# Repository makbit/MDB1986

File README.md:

## MDB1986 - Milandr Development Board for [K1986BE1QI MCU (package LQFP-144)](https://ic.milandr.ru/products/mikrokontrollery_i_protsessory/32_razryadnye_mikrokontrollery/1986vekh_avia/k1986ve1t/).
> This is an open source hardware project for tutorial purposes.

The PCB was designed in the Eagle CAD 9.0.

The [`Blink103`](Blink103) folder contains firmware for on-board debugger MCU (STM32F103). It can be used to test debugger curcuit and target MCU with JTAG IDCODE instruction. Project files were created with the [Keil uVision MDK](https://www.keil.com/demo/eval/arm.htm). The board schematics can be found in [`MDB1986-Schema.png`](MDB1986-Schema.png) file.

### MDB198 Development Board :cool:

## TODO :pen:
- [x] Solder the board :+1:
- [x] Download debugger firmware
- [x] Install [MDR Library Pack](https://ic.milandr.ru/soft/)
- [ ] Build and run Demo test
- [ ] Publish articles!

[GitHub readme tips&tricks](https://help.github.com/articles/basic-writing-and-formatting-syntax/)

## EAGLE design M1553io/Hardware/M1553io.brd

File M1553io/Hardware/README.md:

# M1553io - MIL_STD_1553 input/output shield for MDB1986 Development Board.

This is a simple adapter for connecting the MDB1986 board to the MIL_STD_1553 bus.
It is based on the 5559UH13YA transciever chip by NPO "Physica". This component and transformer can be found in the 5559.lbr file.

##### The adapter board:

##### The adapter schematics:

### TODO :pen:
- [ ] Use small package for 74xxx ICC as a level-shifter;
- [ ] P_EN pin should be pulled-down (or up);
- [ ] Check the length of the transformer pins;
- [ ] Add check-points (pin) for Logic-Analyzer;
- [ ] Place all components on the new Development Board;

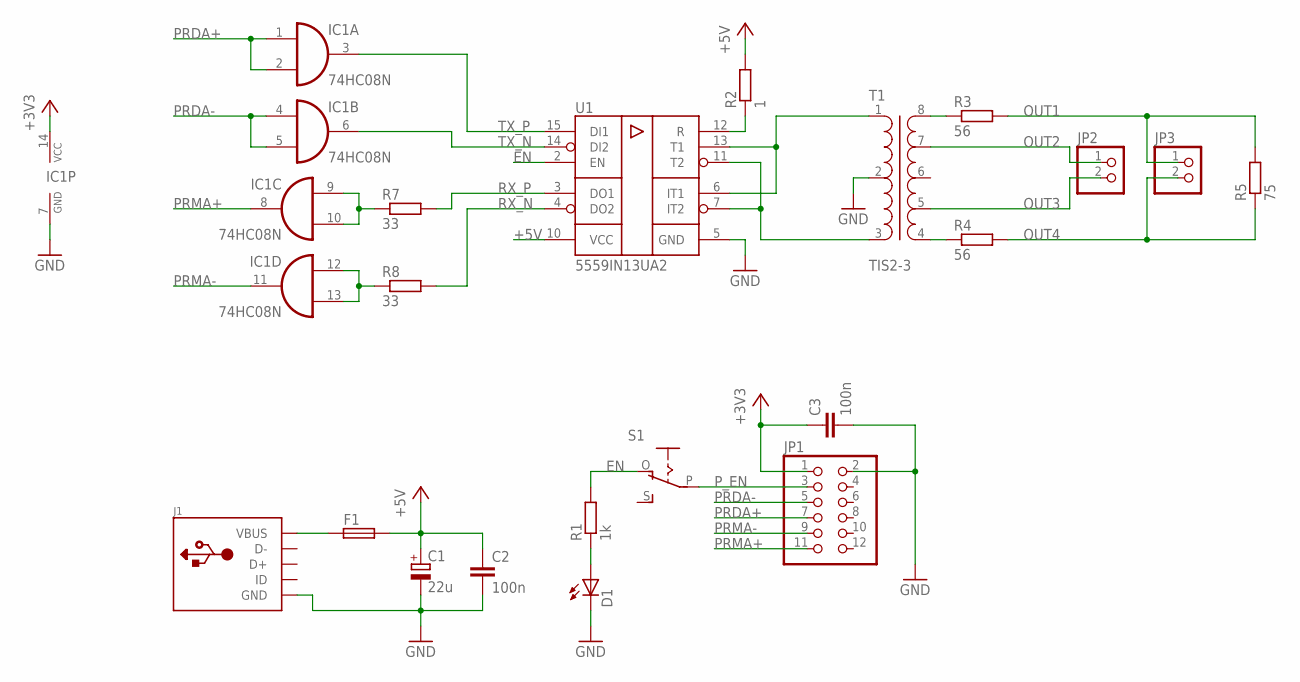
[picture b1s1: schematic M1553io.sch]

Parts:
C1: 22u; RCL-1206F-POL
C2, C3: 100n; RCL-1206F
D1: LED1206; LED-1206F
F1: FUSE-NSMF; RCL-1206F
IC1: 74HC08N; DIL14
J1: USB-MINI; USB-MINIB
JP1: PINHD-2X6; 2X06
JP2, JP3: PINHD-1X2; 1X02
R1: 1k; RCL-0805F
R2: 1; RCL-0805F
R3, R4: 56; RCL-0805F
R5: 75; RCL-0805F
R7, R8: 33; RCL-0805F
S1: EG1218S; EG1218
T1: TIS2-3
U1: 5559IN13UA2; 5119.16-A

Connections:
+3V3: C3.1, IC1.14 (VCC), JP1.1
+5V: C1.+, C2.1, F1.2, R2.2, U1.10 (VCC)
EN: R1.2, S1.O, U1.2 (EN)
GND: C1.-, C2.2, C3.2, D1.C, IC1.7 (GND), J1.GND, JP1.2, T1.2, U1.5 (GND)
unnamed: R3.1, T1.8
unnamed: R4.1, T1.4
unnamed: R2.1, U1.12 (R)
unnamed: F1.1, J1.VBUS
unnamed: D1.A, R1.1
unnamed: IC1.9 (I0), IC1.10 (I1), R7.1
unnamed: IC1.12 (I0), IC1.13 (I1), R8.1
OUT1: JP3.1, R3.2, R5.2
OUT2: JP2.1, T1.7
OUT3: JP2.2, T1.5
OUT4: JP3.2, R4.2, R5.1
PRDA+: IC1.1 (I0), IC1.2 (I1), JP1.7
PRDA-: IC1.4 (I0), IC1.5 (I1), JP1.5
PRMA+: IC1.8 (O), JP1.11
PRMA-: IC1.11 (O), JP1.9
P_EN: JP1.3, S1.P
RX_N: R8.2, U1.4 (DO2)
RX_P: R7.2, U1.3 (DO1)
T1: T1.1, U1.6 (IT1), U1.13 (T1)
T2: T1.3, U1.7 (IT2), U1.11 (T2)
TX_N: IC1.6 (O), U1.14 (DI2)
TX_P: IC1.3 (O), U1.15 (DI1)

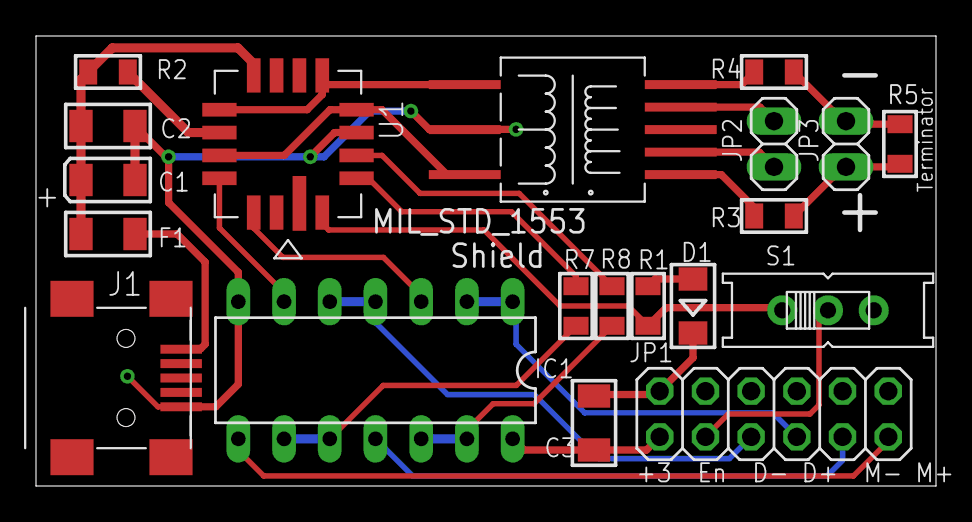
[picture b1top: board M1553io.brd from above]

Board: 2 copper layers, 50.0 x 25.0 mm, 20 parts (0 on the bottom side), 26 nets.

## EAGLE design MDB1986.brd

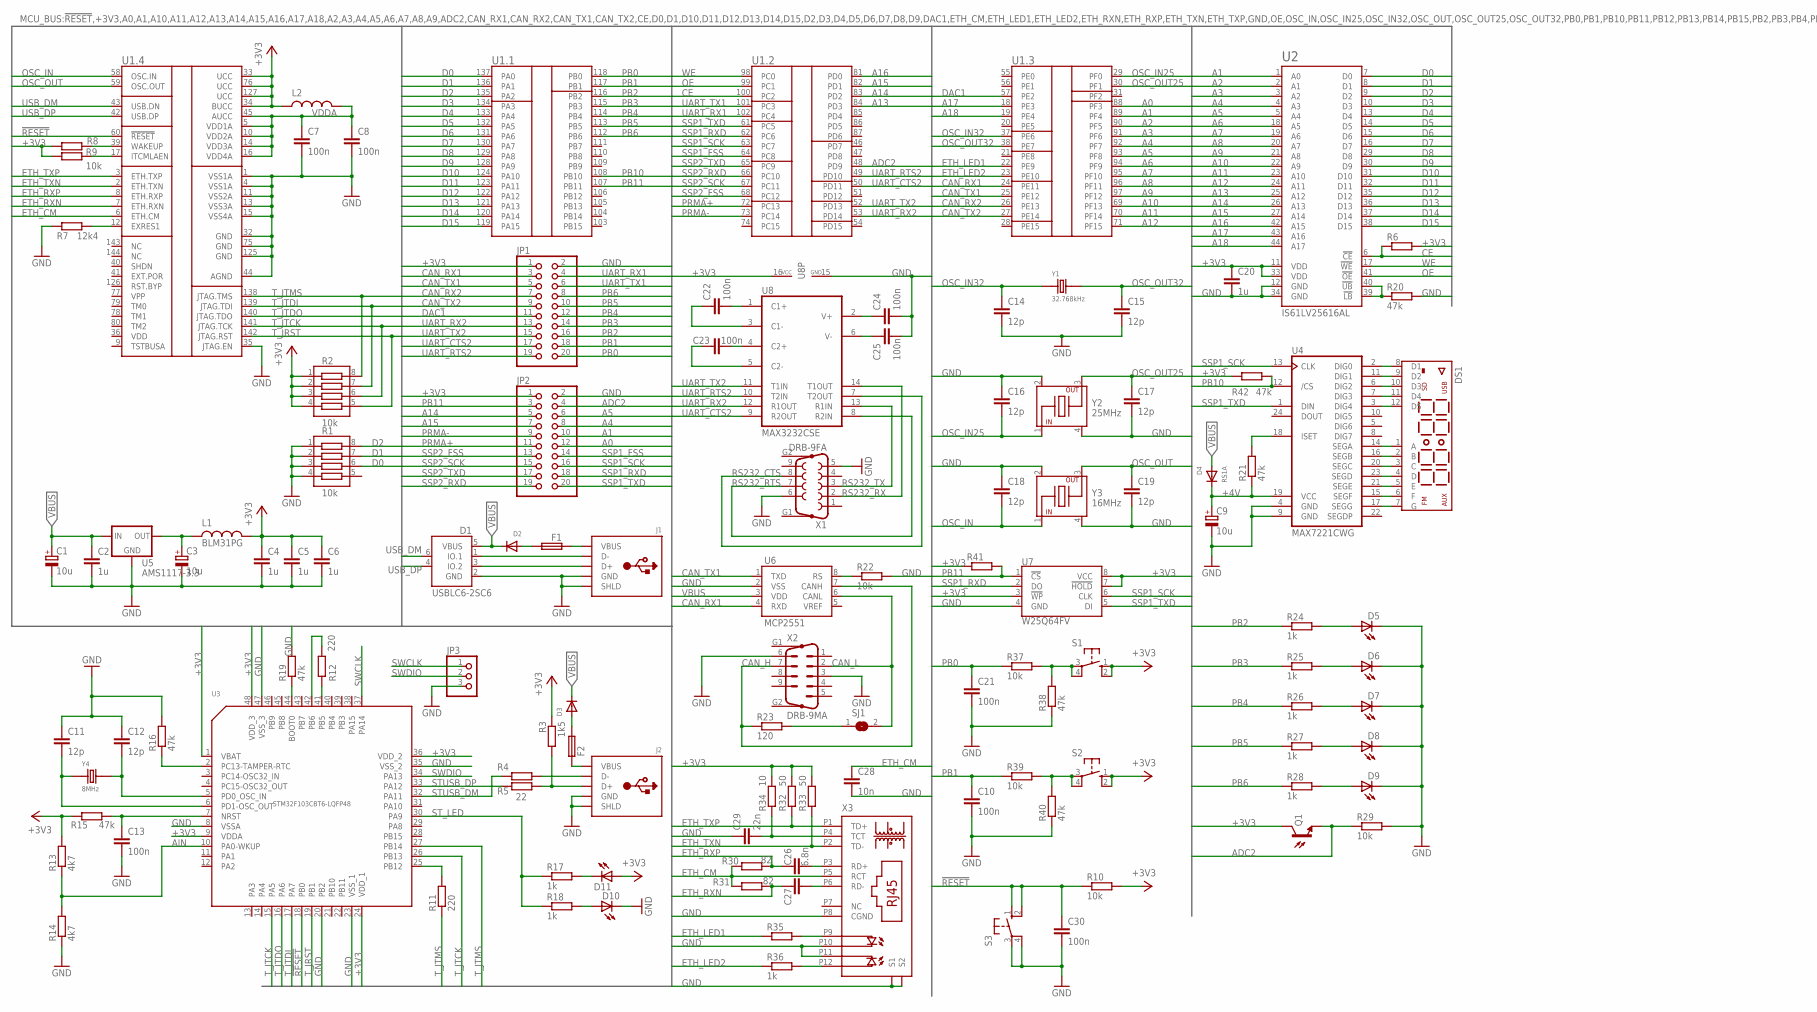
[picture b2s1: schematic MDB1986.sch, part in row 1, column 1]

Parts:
C1, C3, C9: 10u; RCL-1206F-POL
C2, C4, C5, C6, C20: 1u; RCL-0805F
C7, C8, C10, C13, C21, C22, C23, C24, C25, C30: 100n; RCL-0805F
C11, C12, C14, C15, C16, C17, C18, C19: 12p; RCL-0805F
C26: 6.8n; RCL-0805F
C27: C-EU0805; RCL-0805F
C28: 10n; RCL-0805F
C29: 22n; RCL-0805F
D1: USBLC6-2SC6; SOT-23-6L
D2, D3: DIODEDO-214(SMB); DO-214AA(SMB)
D4: RS1A; DO-214AC(SMA)
D5, D6, D7, D8, D9, D10, D11: LED1206; LED-1206F
DS1: LED-7SEG-12PIN-CC; LED-7SEG-12P2.54
F1, F2: FUSE-NSMF; RCL-1206F
J1, J2: USB-TYPE-B; USB-TYPE-B-4P
JP1, JP2: PINHD-2X10; 2X10
JP3: PINHD-1X3; 1X03
L1: BLM31PG; RCL-1206F
L2: L-EU1206; RCL-1206F
Q1: PHOTOTRANSISTORPT17-21C-L41-TR8; PT17-21C-L41-TR8
R1, R2: 10k; RA-1206-X4
R3: 1k5; RCL-0805F
R4, R6, R8, R35, R41: R-EU0805; RCL-0805F
R5: 22; RCL-0805F
R7: 12k4; RCL-0805F
R9, R10, R22, R29, R37, R39: 10k; RCL-0805F
R11, R12: 220; RCL-0805F
R13, R14: 4k7; RCL-0805F
R15, R16, R19, R20, R21, R38, R40, R42: 47k; RCL-0805F
R17, R18, R24, R25, R26, R27, R28, R36: 1k; RCL-0805F
R23: 120; RCL-0805F
R30, R31: 82; RCL-0805F
R32, R33: 50; RCL-0805F
R34: 10; RCL-0805F
S1, S2, S3: SWITCH-10-XX; BUTTON-B3F-10XX
SJ1: SJ
U1: MCU-K1986BE1QI; LQFP144-0.5-20X20M
U2: IS61LV25616AL; TSOP2-44-400BF
U3: STM32F103CBT6-LQFP48; LQFP48-0.5-7X7MM
U4: MAX7221CWG; SO24W
U5: AMS1117-3.3; SOT223
U6: MCP2551; SO08
U7: W25Q64FV; SOIC-8
U8: MAX3232CSE; SO16
X1: DRB-9FA; F09HP
X2: DRB-9MA; M09HP
X3: HR911105A; RJ45
Y1: 32.768kHz; XTAL-FC-135
Y2: 25MHz; XTAL-FA-238
Y3: 16MHz; XTAL-FA-238
Y4: 8MHz; XTAL-NX3225

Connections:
!RESET: C30.1, R10.1, S3.1 (S), S3.2 (S1), U1.60 (!RESET), U3.18 (PB0)
+3V3: C4.1, C5.1, C6.1, C20.1, D11.A, JP1.1, JP2.1, L1.2, L2.1, Q1.C, R2.1 (P.1), R2.2 (P.2), R2.3 (P.3), R2.4 (P.4), R3.1, R6.2, R8.1, R9.1, R10.2, R13.2, R15.1, R32.2, R33.2, R34.2, R41.1, R42.1, S1.1 (S), S1.2 (S1), S2.1 (S), S2.2 (S1), U1.33 (UCC), U1.34 (BUCC), U1.76 (UCC), U1.127 (UCC), U2.11 (VDD), U2.33 (VDD), U3.1 (VBAT), U3.9 (VDDA), U3.24 (VDD_1), U3.36 (VDD_2), U3.48 (VDD_3), U7.3 (!WP), U7.7 (!HOLD), U7.8 (VCC), U8.16 (VCC)
+4V: C9.+, D4.C, R21.1, U4.19 (VCC)
A0: JP2.12, U1.88 (PF3)
A1: JP2.10, U1.89 (PF4), U2.1 (A0)
A2: U1.90 (PF5), U2.2 (A1)
A3: U1.91 (PF6), U2.3 (A2)
A4: JP2.8, U1.92 (PF7), U2.4 (A3)
A5: JP2.6, U1.93 (PF8), U2.5 (A4)
A6: U1.94 (PF9), U2.18 (A5)
A7: U1.95 (PF10), U2.19 (A6)
A8: U1.96 (PF11), U2.20 (A7)
A9: U1.97 (PF12), U2.21 (A8)
A10: U1.69 (PF13), U2.22 (A9)
A11: U1.70 (PF14), U2.23 (A10)
A12: U1.71 (PF15), U2.24 (A11)
A13: U1.84 (PD3), U2.25 (A12)
A14: JP2.5, U1.83 (PD2), U2.26 (A13)
A15: JP2.7, U1.82 (PD1), U2.27 (A14)
A16: U1.81 (PD0), U2.42 (A15)
A17: U1.18 (PE3), U2.43 (A16)
A18: U1.19 (PE4), U2.44 (A17)
ADC2: JP2.4, Q1.E, R29.1, U1.48 (PD9)
AIN: R13.1, R14.2, U3.10 (PA0-WKUP)
BOOT0: R19.1, U3.44 (BOOT0)
CAN_H: R23.1, U6.7 (CANH), X2.7
CAN_L: SJ1.2, U6.6 (CANL), X2.2
CAN_RX1: JP1.3, U1.24 (PE11), U6.4 (RXD)
CAN_RX2: JP1.7, U1.26 (PE13)
CAN_TX1: JP1.5, U1.25 (PE12), U6.1 (TXD)
CAN_TX2: JP1.9, U1.27 (PE14)
CE: R6.1, U1.100 (PC2), U2.6 (!CE)
D0: R1.6 (P.6), U1.137 (PA0), U2.7 (D0)
D1: R1.7 (P.7), U1.136 (PA1), U2.8 (D1)
D2: R1.8 (P.8), U1.135 (PA2), U2.9 (D2)
D3: U1.134 (PA3), U2.10 (D3)
D4: U1.133 (PA4), U2.13 (D4)
D5: U1.132 (PA5), U2.14 (D5)
D6: U1.131 (PA6), U2.15 (D6)
D7: U1.130 (PA7), U2.16 (D7)
D8: U1.129 (PA8), U2.29 (D8)
D9: U1.128 (PA9), U2.30 (D9)
D10: U1.124 (PA10), U2.31 (D10)
D11: U1.123 (PA11), U2.32 (D11)
D12: U1.122 (PA12), U2.35 (D12)
D13: U1.121 (PA13), U2.36 (D13)
D14: U1.120 (PA14), U2.37 (D14)
D15: U1.119 (PA15), U2.38 (D15)
DAC1: JP1.11, U1.57 (PE2)
ETH_CM: C28.1, R30.1, R31.1, U1.6 (ETH.CM), X3.P5 (RCT)
ETH_LED1: R35.1, U1.22 (PE9)
ETH_LED2: R36.1, U1.23 (PE10)
ETH_RXN: C27.1, R31.2, U1.7 (ETH.RXN)
ETH_RXP: C26.1, R30.2, U1.8 (ETH.RXP)
ETH_TXN: R33.1, U1.2 (ETH.TXN), X3.P2 (TD-)
ETH_TXP: R32.1, U1.3 (ETH.TXP), X3.P1 (TD+)
GND: C1.-, C2.2, C3.-, C4.2, C5.2, C6.2, C7.2, C8.2, C9.-, C10.2, C11.1, C12.1, C13.2, C14.2, C15.2, C16.1, C17.2, C18.1, C19.2, C20.2, C21.2, C24.2, C25.2, C28.2, C29.1, C30.2, D1.2 (GND), D5.C, D6.C, D7.C, D8.C, D9.C, D10.C, J1.4_GND (GND), J1.M1 (SHLD), J1.M2 (SHLD), J2.4_GND (GND), J2.M1 (SHLD), J2.M2 (SHLD), JP1.2, JP2.2, JP3.3, R1.1 (P.1), R1.2 (P.2), R1.3 (P.3), R1.4 (P.4), R7.1, R14.1, R16.2, R19.2, R20.2, R22.2, R29.2, R38.1, R40.1, S3.3, S3.4 (P1), U1.1 (VSS1A), U1.4 (VSS1A), U1.11 (VSS2A), U1.13 (VSS3A), U1.15 (VSS4A), U1.32 (GND), U1.35 (JTAG.EN), U1.44 (AGND), U1.75 (GND), U1.125 (GND), U2.12 (GND), U2.34 (GND), U3.8 (VSSA), U3.20 (PB2), U3.23 (VSS_1), U3.35 (VSS_2), U3.47 (VSS_3), U4.4 (GND), U4.9 (GND), U5.1 (GND), U6.2 (VSS), U7.4 (GND), U8.15 (GND), X1.5, X1.6, X2.3, X2.6, X3.P8 (CGND), X3.P10 (GLED-), X3.P11 (YLED-), X3.SHIELD1 (S1), X3.SHIELD2 (S2), Y2.2, Y2.4, Y3.2, Y3.4
unnamed: DS1.8 (D1), U4.2 (DIG0)
unnamed: DS1.9 (D2), U4.11 (DIG1)
unnamed: DS1.10 (D3), U4.6 (DIG2)
unnamed: DS1.11 (D4), U4.7 (DIG3)
unnamed: DS1.12 (D5), U4.3 (DIG4)
unnamed: DS1.1 (A), U4.14 (SEGA)
unnamed: DS1.2 (B), U4.16 (SEGB)
unnamed: DS1.3 (C), U4.20 (SEGC)
unnamed: DS1.4 (D), U4.23 (SEGD)
unnamed: DS1.5 (E), U4.21 (SEGE)
unnamed: DS1.6 (F), U4.15 (SEGF)
unnamed: DS1.7 (G), U4.17 (SEGG)
unnamed: F1.1, J1.1_VBUS (VBUS)
unnamed: D2.A, F1.2
unnamed: C12.2, U3.5 (PD0_OSC_IN), Y4.2
unnamed: C11.2, U3.6 (PD1-OSC_OUT), Y4.1
unnamed: R21.2, U4.18 (ISET)
unnamed: D10.A, R18.2
unnamed: R12.1, U3.41 (PB5)
unnamed: R12.2, U3.42 (PB6)
unnamed: C3.+, L1.1, U5.2 (OUT), U5.4 (OUT)
unnamed: R11.2, U3.25 (PB12)
unnamed: D11.C, R17.2
unnamed: J2.2_DM (D-), R4.1
unnamed: J2.3_DP (D+), R3.2, R5.1
unnamed: C22.2, U8.1 (C1+)
unnamed: F2.1, J2.1_VBUS (VBUS)
unnamed: C13.1, R15.2, U3.7 (NRST)
unnamed: R8.2, U1.39 (WAKEUP)
unnamed: R9.2, U1.17 (ITCMLAEN)
unnamed: C22.1, U8.3 (C1-)
unnamed: R16.1, U3.2 (PC13-TAMPER-RTC)
unnamed: C23.2, U8.4 (C2+)
unnamed: C23.1, U8.5 (C2-)
unnamed: C25.1, U8.6 (V-)
unnamed: C24.1, U8.2 (V+)
unnamed: R20.1, U2.39 (!LB), U2.40 (!UB)
unnamed: R7.2, U1.12 (EXRES1)
unnamed: R23.2, SJ1.1
unnamed: R22.1, U6.8 (RS)
unnamed: D3.A, F2.2
unnamed: D9.A, R28.2
unnamed: D8.A, R27.2
unnamed: D7.A, R26.2
unnamed: R37.2, R38.2, S1.3, S1.4 (P1)
unnamed: D6.A, R25.2
unnamed: D5.A, R24.2
unnamed: C29.2, R34.1, X3.P4 (TCT)
unnamed: R36.2, X3.P12 (YLED+)
unnamed: R35.2, X3.P9 (GLED+)
unnamed: C27.2, X3.P6 (RD-)
unnamed: C26.2, X3.P3 (RD+)
unnamed: R39.2, R40.2, S2.3, S2.4 (P1)
OE: U1.99 (PC1), U2.41 (!OE)
OSC_IN: C18.2, U1.58 (OSC.IN), Y3.1 (X.IN)
OSC_IN25: C16.2, U1.29 (PF0), Y2.1 (X.IN)
OSC_IN32: C14.1, U1.37 (PE6), Y1.1
OSC_OUT: C19.1, U1.59 (OSC.OUT), Y3.3 (X.OUT)
OSC_OUT25: C17.1, U1.30 (PF1), Y2.3 (X.OUT)
OSC_OUT32: C15.1, U1.38 (PE7), Y1.2
PB0: C21.1, JP1.20, R37.1, U1.118 (PB0)
PB1: C10.1, JP1.18, R39.1, U1.117 (PB1)
PB2: JP1.16, R24.1, U1.116 (PB2)
PB3: JP1.14, R25.1, U1.115 (PB3)
PB4: JP1.12, R26.1, U1.114 (PB4)
PB5: JP1.10, R27.1, U1.113 (PB5)
PB6: JP1.8, R28.1, U1.112 (PB6)
PB10: R42.2, U1.108 (PB10), U4.12 (/CS)
PB11: JP2.3, R41.2, U1.107 (PB11), U7.1 (!CS)
PRMA+: JP2.11, U1.72 (PC13)
PRMA-: JP2.9, U1.73 (PC14)
RS232_CTS: U8.7 (T2OUT), X1.8
RS232_RTS: U8.8 (R2IN), X1.7
RS232_RX: U8.14 (T1OUT), X1.2
RS232_TX: U8.13 (R1IN), X1.3
SSP1_FSS: JP2.14, U1.64 (PC8)
SSP1_RXD: JP2.18, U1.62 (PC6), U7.2 (DO)
SSP1_SCK: JP2.16, U1.63 (PC7), U4.13 (CLK), U7.6 (CLK)
SSP1_TXD: JP2.20, U1.61 (PC5), U4.1 (DIN), U7.5 (DI)
SSP2_FSS: JP2.13, U1.68 (PC12)
SSP2_RXD: JP2.19, U1.66 (PC10)
SSP2_SCK: JP2.15, U1.67 (PC11)
SSP2_TXD: JP2.17, U1.65 (PC9)
STUSB_DM: R4.2, U3.32 (PA11)
STUSB_DP: R5.2, U3.33 (PA12)
ST_LED: R17.1, R18.1, U3.30 (PA9)
SWCLK: JP3.1, U3.37 (PA14)
SWDIO: JP3.2, U3.34 (PA13)
T_JRST: R2.5 (P.5), U1.142 (JTAG.RST), U3.19 (PB1)
T_JTCK: R2.6 (P.6), U1.141 (JTAG.TCK), U3.15 (PA5), U3.26 (PB13)
T_JTDI: R2.7 (P.7), U1.139 (JTAG.TDI), U3.17 (PA7)
T_JTDO: U1.140 (JTAG.TDO), U3.16 (PA6)
T_JTMS: R2.8 (P.8), R11.1, U1.138 (JTAG.TMS), U3.27 (PB14)
UART_CTS2: JP1.17, U1.50 (PD11), U8.9 (R2OUT)
UART_RTS2: JP1.19, U1.49 (PD10), U8.10 (T2IN)
UART_RX1: JP1.4, U1.102 (PC4)
UART_RX2: JP1.13, U1.53 (PD14), U8.12 (R1OUT)
UART_TX1: JP1.6, U1.101 (PC3)
UART_TX2: JP1.15, U1.52 (PD13), U8.11 (T1IN)
USB_D+: D1.3 (IO.2), J1.3_DP (D+)
USB_D-: D1.1 (IO.1), J1.2_DM (D-)
USB_DM: D1.6 (IO_1), U1.43 (USB.DN)
USB_DP: D1.4 (IO_2), U1.42 (USB.DP)
VBUS: C1.+, C2.1, D1.5 (VBUS), D2.C, D3.C, D4.A, U5.3 (IN), U6.3 (VDD)
VDDA: C7.1, C8.1, L2.2, U1.5 (VDD1A), U1.10 (VDD2A), U1.14 (VDD3A), U1.16 (VDD4A), U1.45 (AUCC)
WE: U1.98 (PC0), U2.17 (!WE)

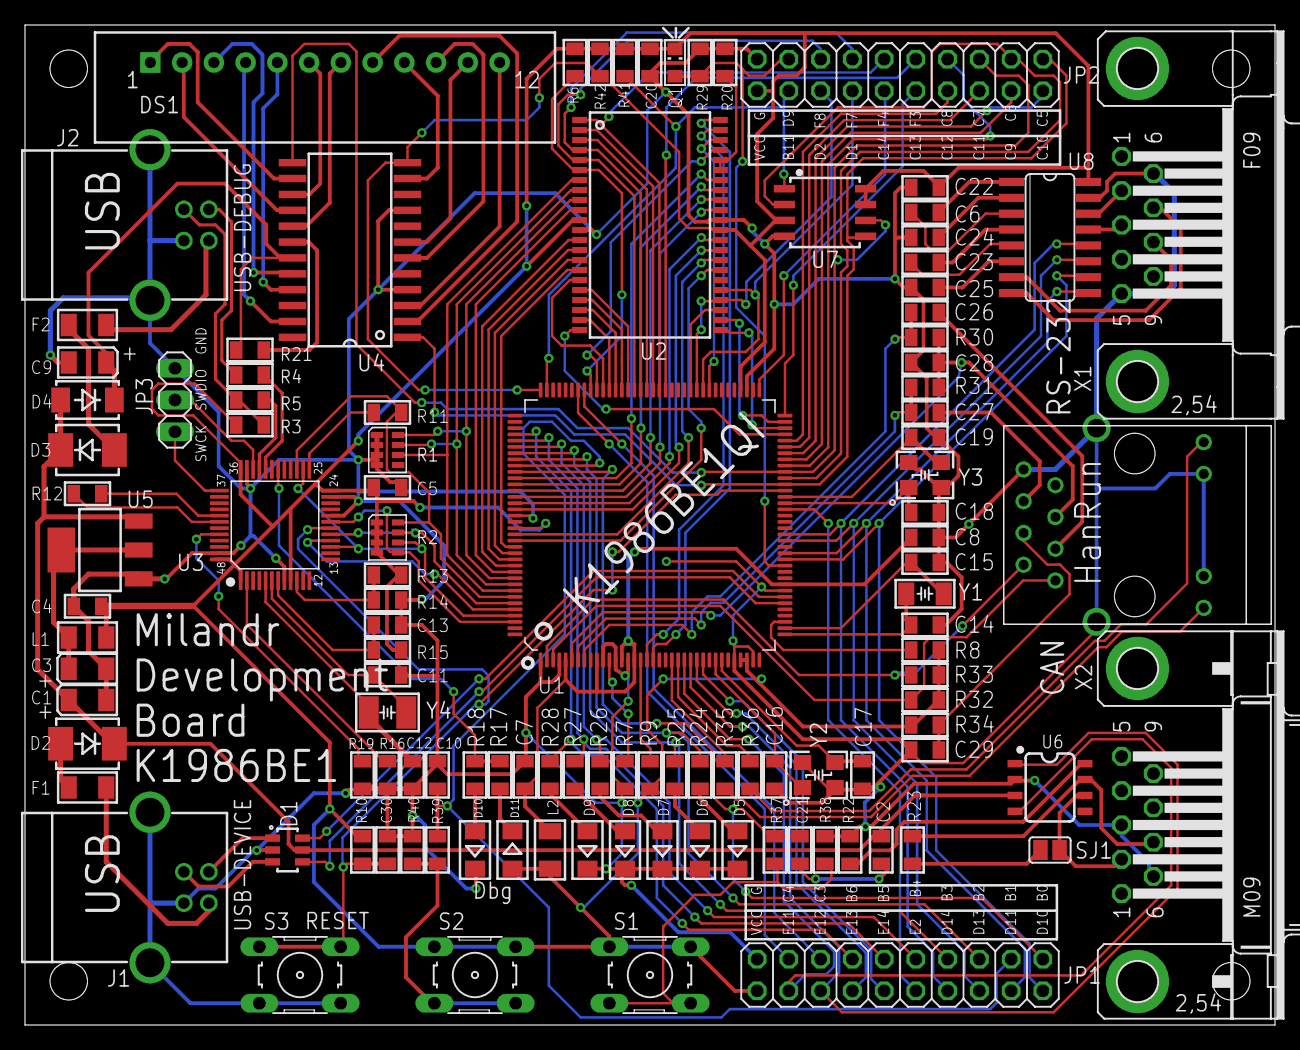
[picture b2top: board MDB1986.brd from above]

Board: 2 copper layers, 100.0 x 80.0 mm, 113 parts (0 on the bottom side), 163 nets.

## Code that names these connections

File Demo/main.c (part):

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
	PORT_StructInit (&initStruct);
	//--------------------------------------------//
	// DATA PA0..PA15 (D0..D15)                   //
	//--------------------------------------------//
	initStruct.PORT_MODE      = PORT_MODE_DIGITAL;
	initStruct.PORT_PD_SHM    = PORT_PD_SHM_ON;
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	initStruct.PORT_Pin       = PORT_Pin_All;
	PORT_Init (MDR_PORTA, &initStruct);	
	//--------------------------------------------//
	// Address PF3-PF15 (A0..A12), A0 - not used. //
	//--------------------------------------------//
	initStruct.PORT_FUNC      = PORT_FUNC_ALTER;
	initStruct.PORT_Pin       = PORT_Pin_4  | PORT_Pin_5  |
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	                            PORT_Pin_14 | PORT_Pin_15;
	PORT_Init (MDR_PORTF, &initStruct);	
	//--------------------------------------------//
	// Address PD3..PD0 (A13..A16)                //
	//--------------------------------------------//
	initStruct.PORT_FUNC      = PORT_FUNC_OVERRID;
	initStruct.PORT_Pin       = PORT_Pin_0 | PORT_Pin_1 |
	                            PORT_Pin_2 | PORT_Pin_3;
	PORT_Init (MDR_PORTD, &initStruct);	
	//--------------------------------------------//
	// Address PE3, PE4 (A17, A18)                //
	//--------------------------------------------//
	initStruct.PORT_FUNC      = PORT_FUNC_ALTER;
	initStruct.PORT_Pin       = PORT_Pin_3 | PORT_Pin_4;
	PORT_Init (MDR_PORTE, &initStruct);	
	//--------------------------------------------//
	// Control PC0,PC1 (nWE,nOE)                  //
	//--------------------------------------------//
	initStruct.PORT_FUNC      = PORT_FUNC_MAIN;
	initStruct.PORT_Pin       = PORT_Pin_0 | PORT_Pin_1;
	PORT_Init (MDR_PORTC, &initStruct);	
	//--------------------------------------------//
	// Control PC2 (nCE)                          //
	//--------------------------------------------//
	initStruct.PORT_PD        = PORT_PD_DRIVER;
	initStruct.PORT_OE        = PORT_OE_OUT;
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
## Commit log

2019-07-04 Initial release
2019-07-04 Component library for MakBit hardware projects.
2019-12-26 Add files via upload
    Led blinking & JTAG IDCode reader for custom ST-Link.
2019-12-26 Milandr Development Board 1986 Schematics
2019-12-26 Gerber files ready for production (tested).
2019-12-26 MDR1986 MCU Package
2019-12-29 MDB1986 Development Board
2020-08-31 This hardware was assembled and tested.
2022-03-08 Initial upload
2022-03-08 ModBus RTU demo
2023-01-13 Example project to test Ethernet hardware

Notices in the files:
M1553io/Hardware/M1553io.brd:
https://makbit.com (c) 2020
